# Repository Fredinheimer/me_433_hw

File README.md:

# me_433_hw
Homework for Michael Hendon in ME 433

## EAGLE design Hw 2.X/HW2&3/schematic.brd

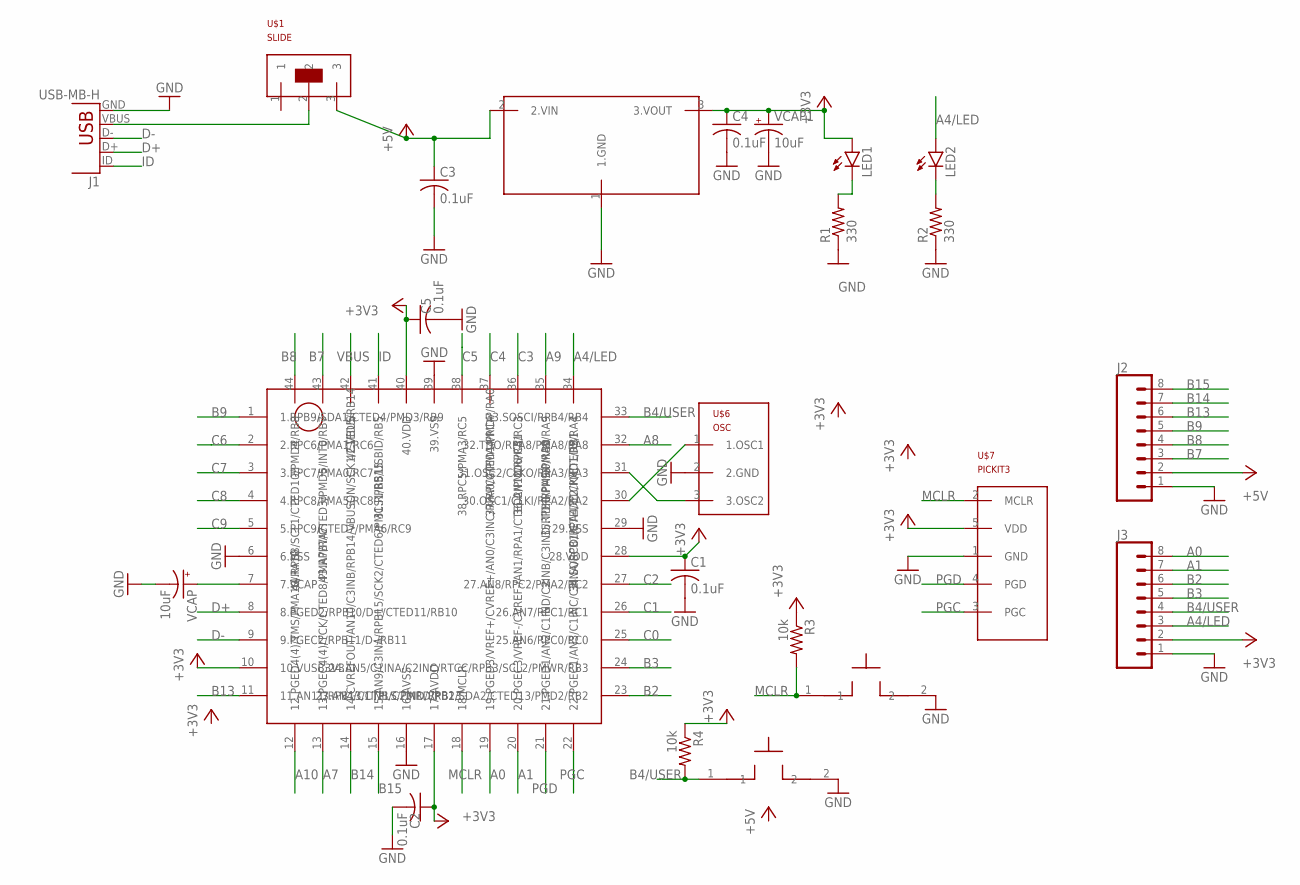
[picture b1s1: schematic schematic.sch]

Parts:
C1, C2, C3, C4, C5: 0.1uF; C025-025X050
J1: USB-MB-H
J2, J3: CONN_08"; 1X08
LED1, LED2: LED3MM
R1, R2: 330; 0207/10
R3, R4: 10k; 0207/10
RESET: BUTTON
U$1: SLIDE; SWITCH
U$2: PIC32MX; TQFP44
U$3: TO92VOLTREG; TO92
U$6: OSC
U$7: PICKIT3; 1X05
USER: BUTTON
VCAP, VCAP1: 10uF; B45181B

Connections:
+3V3: C1.1, C2.1, C4.1, C5.1, J3.2, LED1.A, R3.1, R4.1, U$2.10 (10.VUSB3V3), U$2.17 (17.AVDD), U$2.28 (28.VDD), U$2.40 (40.VDD), U$3.3 (3.VOUT), U$7.5 (VDD), VCAP1.+
A0: J3.8, U$2.19 (19.PGED3/VREF+/CVREF+/AN0/C3INC/RPA0/CT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)
A1: J3.7, U$2.20 (20.PGEC3/VREF-/CVREF-/AN1/RPA1/CTED2/PM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)
A4/LED: J3.3, LED2.A, U$2.34 (34.SOSCO/RPA4/T1CK/CTED9/RA4)
A7: U$2.13 (13.PGEC4(4)/TCK/CTED8/PMA7/RA7)
A8: U$2.32 (32.TDO/RPA8/PMA8/RA8)
A9: U$2.35 (35.TDI/RPA9/PMA9/RA9)
A10: U$2.12 (12.PGED4(4)/TMS/PMA10/RA10)
B2: J3.6, U$2.23 (23.AN4/C1INB/C2IND/RPB2/SDA2/CTED13/PMD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)
B3: J3.5, U$2.24 (24.AN5/C1INA/C2INC/RTCC/RPB3/SCL2/PMWR/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)
B4/USER: J3.4, R4.2, U$2.33 (33.SOSCI/RPB4/RB4), USER.1
B7: J2.3, U$2.43 (43.RPB7/CTED3/PMD5/INT0/RB7)
B8: J2.4, U$2.44 (44.RPB8/SCL1/CTED10/PMD4/RB8)
B9: J2.5, U$2.1 (1.RPB9/SDA1/CTED4/PMD3/RB9)
B13: J2.6, U$2.11 (11.AN11/RPB13/CTPLS/PMRD/RB13)
B14: J2.7, U$2.14 (14.CVREFOUT/AN10/C3INB/RPB14/VBUSON/SCK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)
B15: J2.8, U$2.15 (15.AN9/C3INA/RPB15/SCK2/CTED6/PMCS1/RB15)
C0: U$2.25 (25.AN6/RPC0/RC0)
C1: U$2.26 (26.AN7/RPC1/RC1)
C2: U$2.27 (27.AN8/RPC2/PMA2/RC2)
C3: U$2.36 (36.AN12/RPC3/RC3)
C4: U$2.37 (37.RPC4/PMA4/RC4)
C5: U$2.38 (38.RPC5/PMA3/RC5)
C6: U$2.2 (2.RPC6/PMA1/RC6)
C7: U$2.3 (3.RPC7/PMA0/RC7)
C8: U$2.4 (4.RPC8/PMA5/RC8)
C9: U$2.5 (5.RPC9/CTED7/PMA6/RC9)
D+: J1.D+, U$2.8 (8.PGED2/RPB10/D+/CTED11/RB10)
D-: J1.D-, U$2.9 (9.PGEC2/RPB11/D-/RB11)
GND: C1.2, C2.2, C3.2, C4.2, C5.2, J1.GND, J2.1, J3.1, R1.1, R2.1, RESET.2, U$2.6 (6.VSS), U$2.16 (16.AVSS), U$2.29 (29.VSS), U$2.39 (39.VSS), U$3.1 (1.GND), U$6.2 (2.GND), U$7.1 (GND), USER.2, VCAP.-, VCAP1.-
ID: J1.ID (D+1), U$2.41 (31.RPB5/USBID/RB5)
MCLR: R3.2, RESET.1, U$2.18 (18.MCLR), U$7.2 (MCLR)
unnamed: J1.VBUS, U$1.2
unnamed: LED1.K (C), R1.2
unnamed: U$2.30 (30.OSC1/CLKI/RPA2/RA2), U$6.1 (1.OSC1)
unnamed: U$2.31 (31.OSC2/CLKO/RPA3/RA3), U$6.3 (3.OSC2)
unnamed: U$2.7 (7.VCAP), VCAP.+
unnamed: LED2.K (C), R2.2
PGC: U$2.22 (22.PGEC1/AN3/C1INC/C2INA/RPB1/CTED12/PM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), U$7.3 (PGC)
PGD: U$2.21 (21.PGED1/AN2/C1IND/C2INB/C3IND/RPB0/PMD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), U$7.4 (PGD)

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
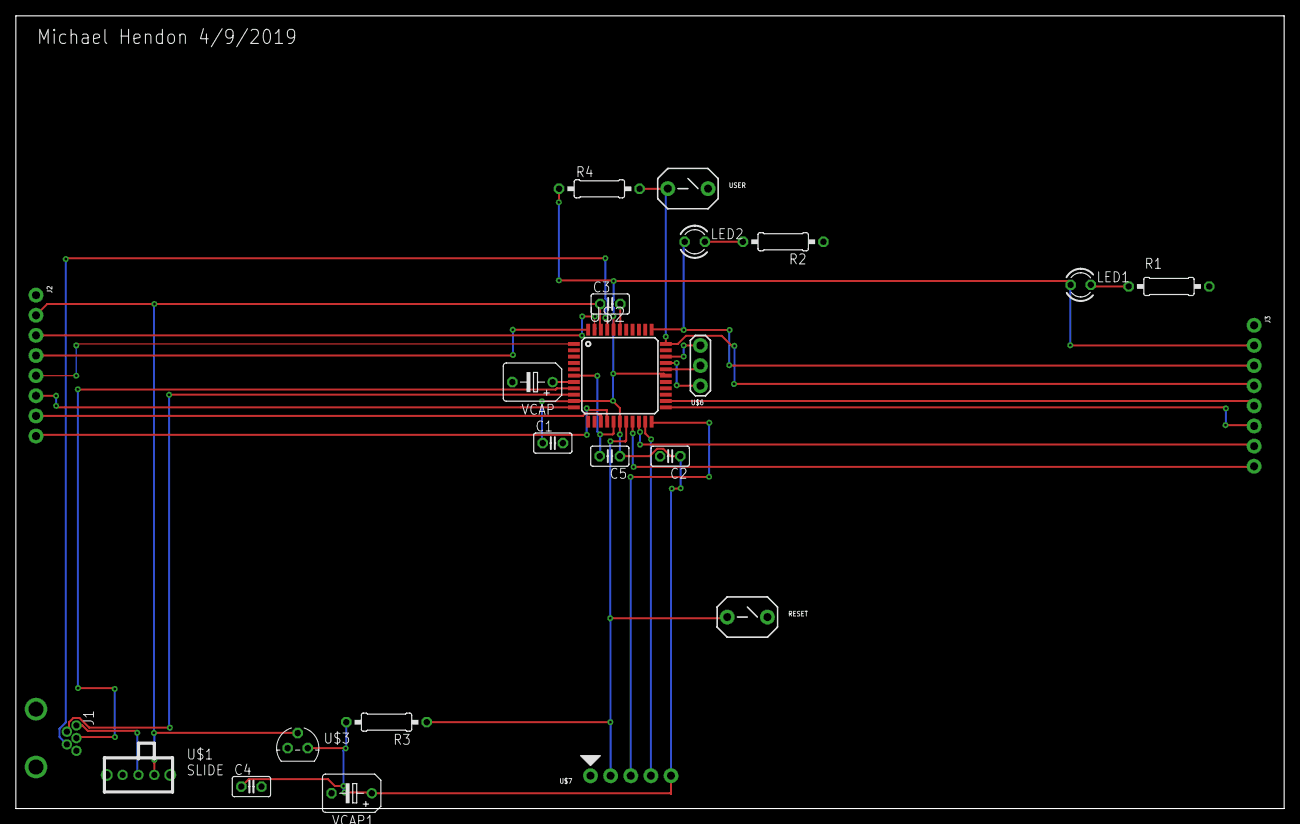
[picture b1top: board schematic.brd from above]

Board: 2 copper layers, 160.0 x 100.0 mm, 23 parts (0 on the bottom side), 27 nets.

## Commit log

2019-04-02 Started HW1
2019-04-02 pictures
2019-04-02 Update Main.c
    began changing variables
2019-04-03 Fixed Main
    previous main not recognized as c file
    also added code for 1khz signal
2019-04-03 Adjustments to Main
    messed around trying to program, currently can't do TRIS or LAT commands
2019-04-03 Tried Nick's Method for fixing
    added in ANSELA and ANSELB
2019-04-03 working version
    working version finished after adding test from nick
2019-04-03 Create ME433HW1Demo.mp4
    Added demo video
2019-04-03 fixed video
2019-04-08 hw2
    made library and schematic
2019-04-09 renamed
2019-04-09 rename for eagle
2019-04-11 Made Board
2019-04-11 adjust board
2019-04-13 began mcp work
    adjusted sample code from book
2019-04-13 tested output (weird waves)
2019-04-15 added pictures
2019-04-16 minor change
2019-04-17 got led working
2019-04-18 fixed and finished led change
2019-04-19 did hw6
2019-04-24 started HW7
2019-04-24 added demo video
2019-04-25 HW 8
2019-05-02 HW9 added
2019-05-06 HW 10 finished
2019-05-08 HW11
2019-05-16 HW 12 and HW 13 CAD
2019-05-16 added DXFs
2019-05-21 Added HW 14
2019-05-30 HW15
2019-06-14 tech cup
